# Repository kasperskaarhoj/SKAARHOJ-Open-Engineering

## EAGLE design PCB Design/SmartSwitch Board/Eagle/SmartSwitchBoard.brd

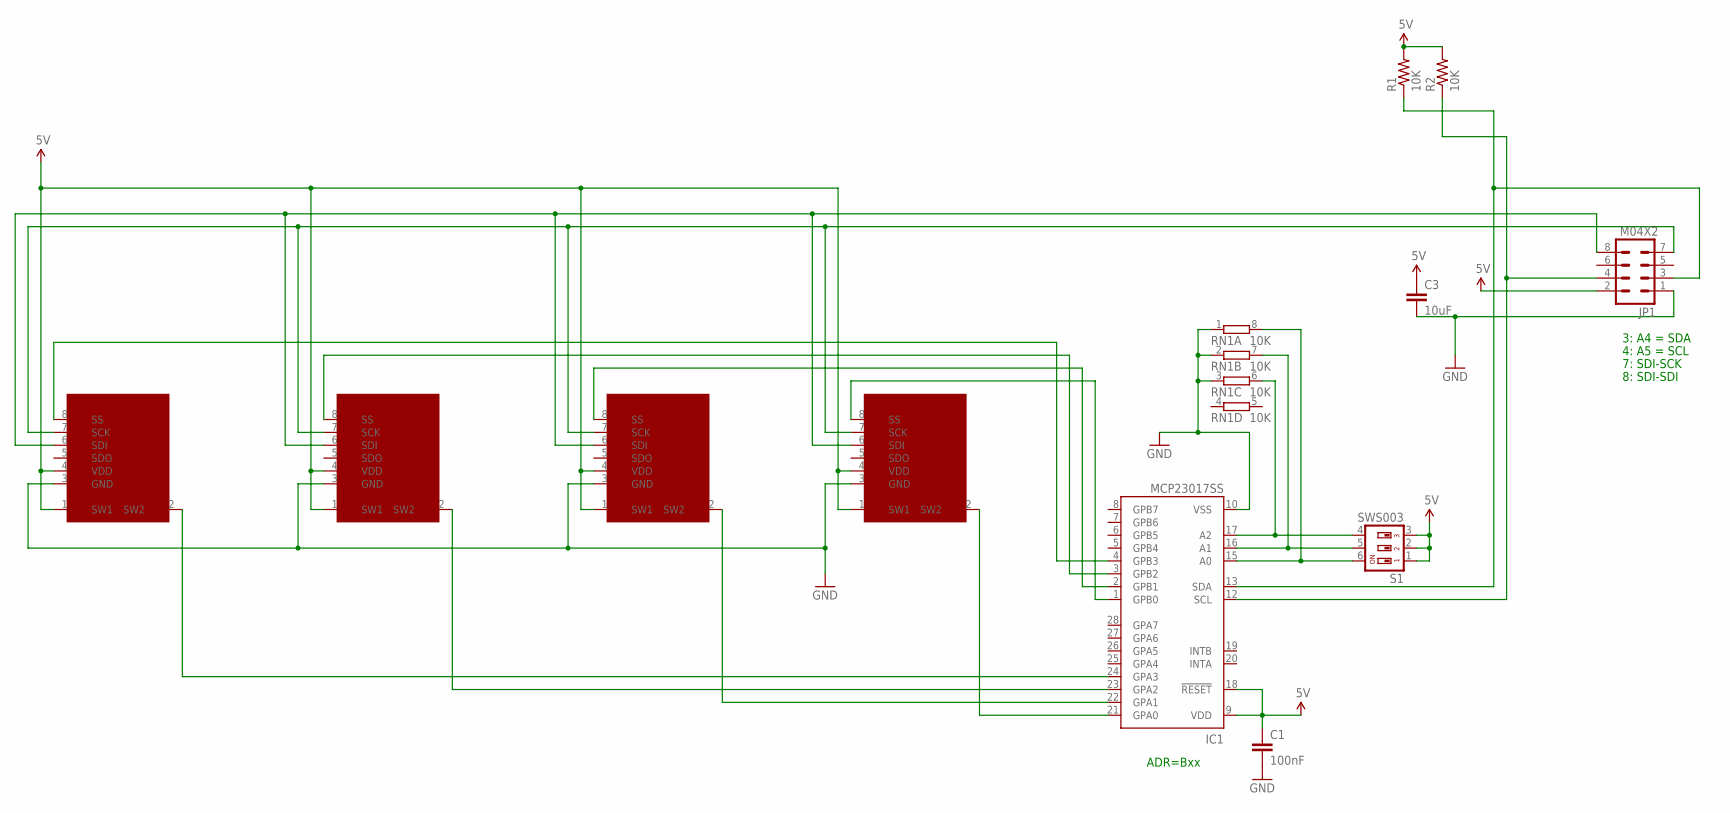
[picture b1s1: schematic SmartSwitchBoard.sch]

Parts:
C1: 100nF; 0603-CAP
C3: 10uF; 0805
IC1: MCP23017SS; SSOP28; MPN MCP23017-E/SS
JP1: M04X2; 2X4
R1, R2: 10K; 0603-RES
RN1: 10K; CAY16_HAND
S1: SWS003; SMS-003
U$3, U$4, U$5, U$6: SMART_SWITCH

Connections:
5V: C1.1, C3.1, IC1.9 (VDD), IC1.18 (!RESET), JP1.2, R1.2, R2.2, S1.1, S1.2, S1.3, U$3.1 (SW1), U$3.4 (VDD), U$4.1 (SW1), U$4.4 (VDD), U$5.1 (SW1), U$5.4 (VDD), U$6.1 (SW1), U$6.4 (VDD)
GND: C1.2, C3.2, IC1.10 (VSS), JP1.1, RN1.1, RN1.2 (1), RN1.3 (1), U$3.3 (GND), U$4.3 (GND), U$5.3 (GND), U$6.3 (GND)
unnamed: IC1.15 (A0), RN1.8 (2), S1.6
unnamed: IC1.16 (A1), RN1.7 (2), S1.5
unnamed: IC1.13 (SDA), JP1.3, R1.1
unnamed: IC1.17 (A2), RN1.6 (2), S1.4
unnamed: IC1.12 (SCL), JP1.4, R2.1
unnamed: JP1.7, U$3.7 (SCK), U$4.7 (SCK), U$5.7 (SCK), U$6.7 (SCK)
unnamed: JP1.8, U$3.6 (SDI), U$4.6 (SDI), U$5.6 (SDI), U$6.6 (SDI)
unnamed: IC1.1 (GPB0), U$3.8 (SS)
unnamed: IC1.2 (GPB1), U$4.8 (SS)
unnamed: IC1.3 (GPB2), U$5.8 (SS)
unnamed: IC1.4 (GPB3), U$6.8 (SS)
unnamed: IC1.24 (GPA3), U$6.2 (SW2)
unnamed: IC1.23 (GPA2), U$5.2 (SW2)
unnamed: IC1.21 (GPA0), U$3.2 (SW2)
unnamed: IC1.22 (GPA1), U$4.2 (SW2)

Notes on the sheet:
4: A5 = SCL
3: A4 = SDA
ADR=Bxx
7: SDI-SCK
8: SDI-SDI

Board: 2 copper layers, 12 parts (8 on the bottom side), 17 nets, no tracks yet.

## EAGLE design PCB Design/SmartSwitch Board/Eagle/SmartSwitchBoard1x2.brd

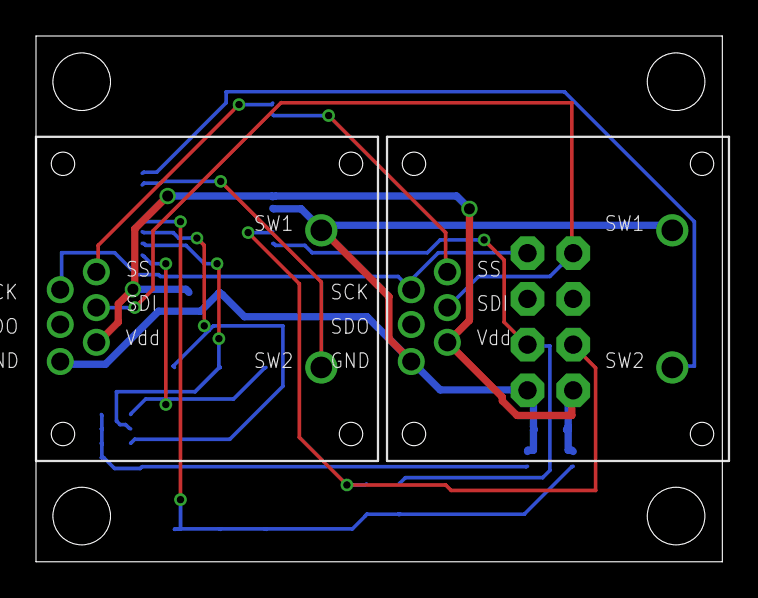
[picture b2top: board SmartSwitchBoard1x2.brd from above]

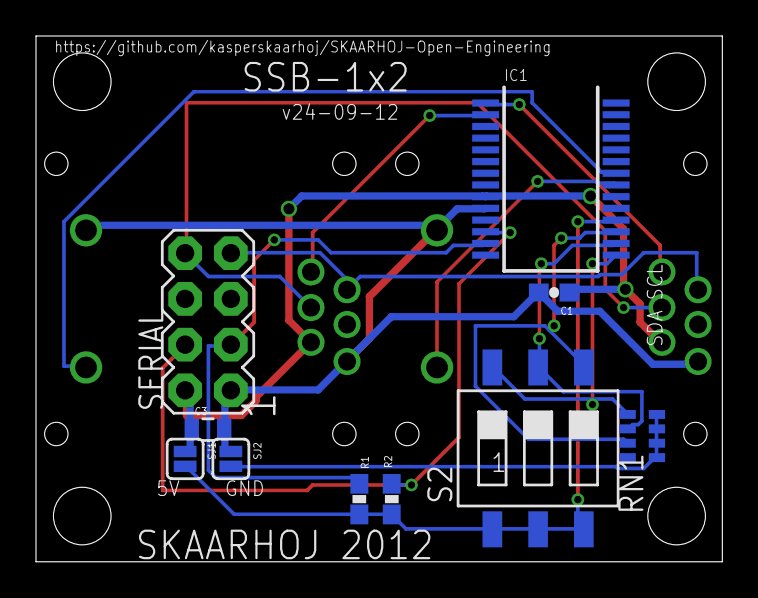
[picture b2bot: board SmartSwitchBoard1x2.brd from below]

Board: 2 copper layers, 38.1 x 29.2 mm, 12 parts (10 on the bottom side), 15 nets.

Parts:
C1: 100nF; 0603-CAP
C3: 10uF; 0805
IC1: MCP23017SS; SSOP28
R1, R2: 10K; 0603-RES
RN1: 10K; CAY16_HAND
S2: SWS003; SMS-003
SERIAL: M04X2; 2X4
SJ1, SJ2: SOLDERJUMPERNC; SJ_2S
U$2, U$3: SMART_SWITCHSMART_SWITCH_8PIN; SMART_SWITCH

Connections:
5V: C1.2, C3.1, IC1.9, SERIAL.2, SJ1.1, U$2.4, U$3.4
5VL: IC1.18, R1.1, R2.1, S2.1, S2.2, S2.3, SJ1.2
A0: IC1.15, RN1.5, S2.6
A1: IC1.16, RN1.6, S2.5
A2: IC1.17, RN1.7, S2.4
GND: C1.1, C3.2, IC1.10, SERIAL.1, SJ2.1, U$2.1, U$2.3, U$3.1, U$3.3
GNDL: RN1.1, RN1.2, RN1.3, RN1.4, SJ2.2
GPA0: IC1.21, U$2.2
GPA1: IC1.22, U$3.2
GPB0: IC1.1, U$2.8
GPB1: IC1.2, U$3.8
I2C_SCL: IC1.12, R2.2, SERIAL.4
I2C_SDA: IC1.13, R1.2, SERIAL.3
SDI_MOSI: SERIAL.8, U$2.6, U$3.6
SDI_SCLK: SERIAL.7, U$2.7, U$3.7

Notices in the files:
parts and their libraries:
SparkFun: Licensing: CC v3.0 Share-Alike You are welcome to use this library for commercial purposes.
